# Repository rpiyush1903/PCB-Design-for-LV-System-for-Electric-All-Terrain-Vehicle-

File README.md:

# e-ATV Vehicle Control Unit (VCU)

## What this is

This is the Vehicle Control Unit (VCU) for our electric All-Terrain Vehicle, engineered specifically for the demands of e-BAJA SAE competition . The control unit should be resistant to high vibration, rough terrain, electrical noise etc.

The VCU sits at the center of the car's low-voltage control system. It reads every driver input ,ignition Key, cockpit and chassis kill switches, brake pressure switch, accelerator position sensor, and Forward/Neutral/Reverse selection(Rotary Switch) and turns that into safe, Low Voltage control over the high-voltage tractive system. It continuously monitors the safety loop, runs the basic starting and running logic of the vehicle , Controls all the Low Voltage and High Voltage components in the vehicle and is built to shut the whole tractive system down immediately if anything looks wrong.

## Hardware Design & PCB Architecture
The whole electrical layout is built with the idea of Simple , Efficient Control and Robust Safety 

The VCU PCB is made to protect the ATmega328P microcontroller from high-voltage transients, high-current switching noise, and off-road mechanical vibration through strategic domain isolation and multi-stage output driving.

## 1. Power Distribution & System Isolation

### 48V Tractive System
Powers the motor controller through a 160A main fuse, HV cut-off switch, and main Accumulator Isolation Relays (AIRs).

### 12V LV System
Stepped down via a 48V-to-12V DC-DC converter to power external safety loops, lights, RTDS buzzer, and relay coils.

### 5V Logic System
Generated by a dedicated 12V-to-5V buck converter with electrolytic (100 µF) and ceramic (0.1 µF) decoupling capacitors, providing clean power exclusively to the MCU and sensor pull-up networks.

## 2. Optocoupler & Active-LOW Output Drive

### Active-LOW Logic
GPIO output pins require  0V (LOW) signal to energize outputs. Floating pin states during bootloader execution or CPU resets cannot accidentally trigger relays.

### Galvanic Isolation
Output pins drive PC817 optocouplers, creating an optical barrier between the 5V MCU logic ground and the 12V relay ground plane.

### Low-Side Switching
Optocoupler phototransistors trigger BC547 NPN transistors to sink 12V relay coil current, keeping high current draw entirely off the 5V logic rail.

### Flyback Diode Clamping
1N4007 flyback diodes are placed in reversed manner and parallel across all relay coils to safely dissipate back-EMF inductive voltage spikes ($V = -L \frac{di}{dt}$) during de-energization, preventing CMOS latch-up.

### Digital Inputs
Brake pressure switch (A3), FNR selectors (A4/A5), and safety interlocks (A1) utilize pull-down resistor networks and hardware debouncing to guarantee stable state detection across rough terrain.

### Power Distribution

* **High Voltage Rail:** The 48V accumulator feeds through a 160A main fuse and an HV cut-off switch straight to the motor controller.
* **Low Voltage Rail:** A 48V→12V DC-DC converter powers the vehicle's 12V accessories and the dashboard safety loop.
* **Logic Power:** The ATmega328P and its supporting logic get their own dedicated 12V→5V buck converter, kept isolated from everything else on the low-voltage side.

### Core Components

* **MCU:** ATmega328P
* **Sensor Inputs:** Ignition key, cockpit and chassis kill switches, brake pressure switch, accelerator (Hall-effect sensor), and the Forward/Neutral/Reverse selector all fed from the dashboard cluster.
* **Actuator Outputs:** Relay-driven outputs for the TSAL, reverse light, main contactor (accumulator isolation relay), brake light, and the RTDS buzzer.

## Firmware Architecture

The firmware (C++, compiled through Arduino) is built with the starting sequence in mind and safety as a priority .

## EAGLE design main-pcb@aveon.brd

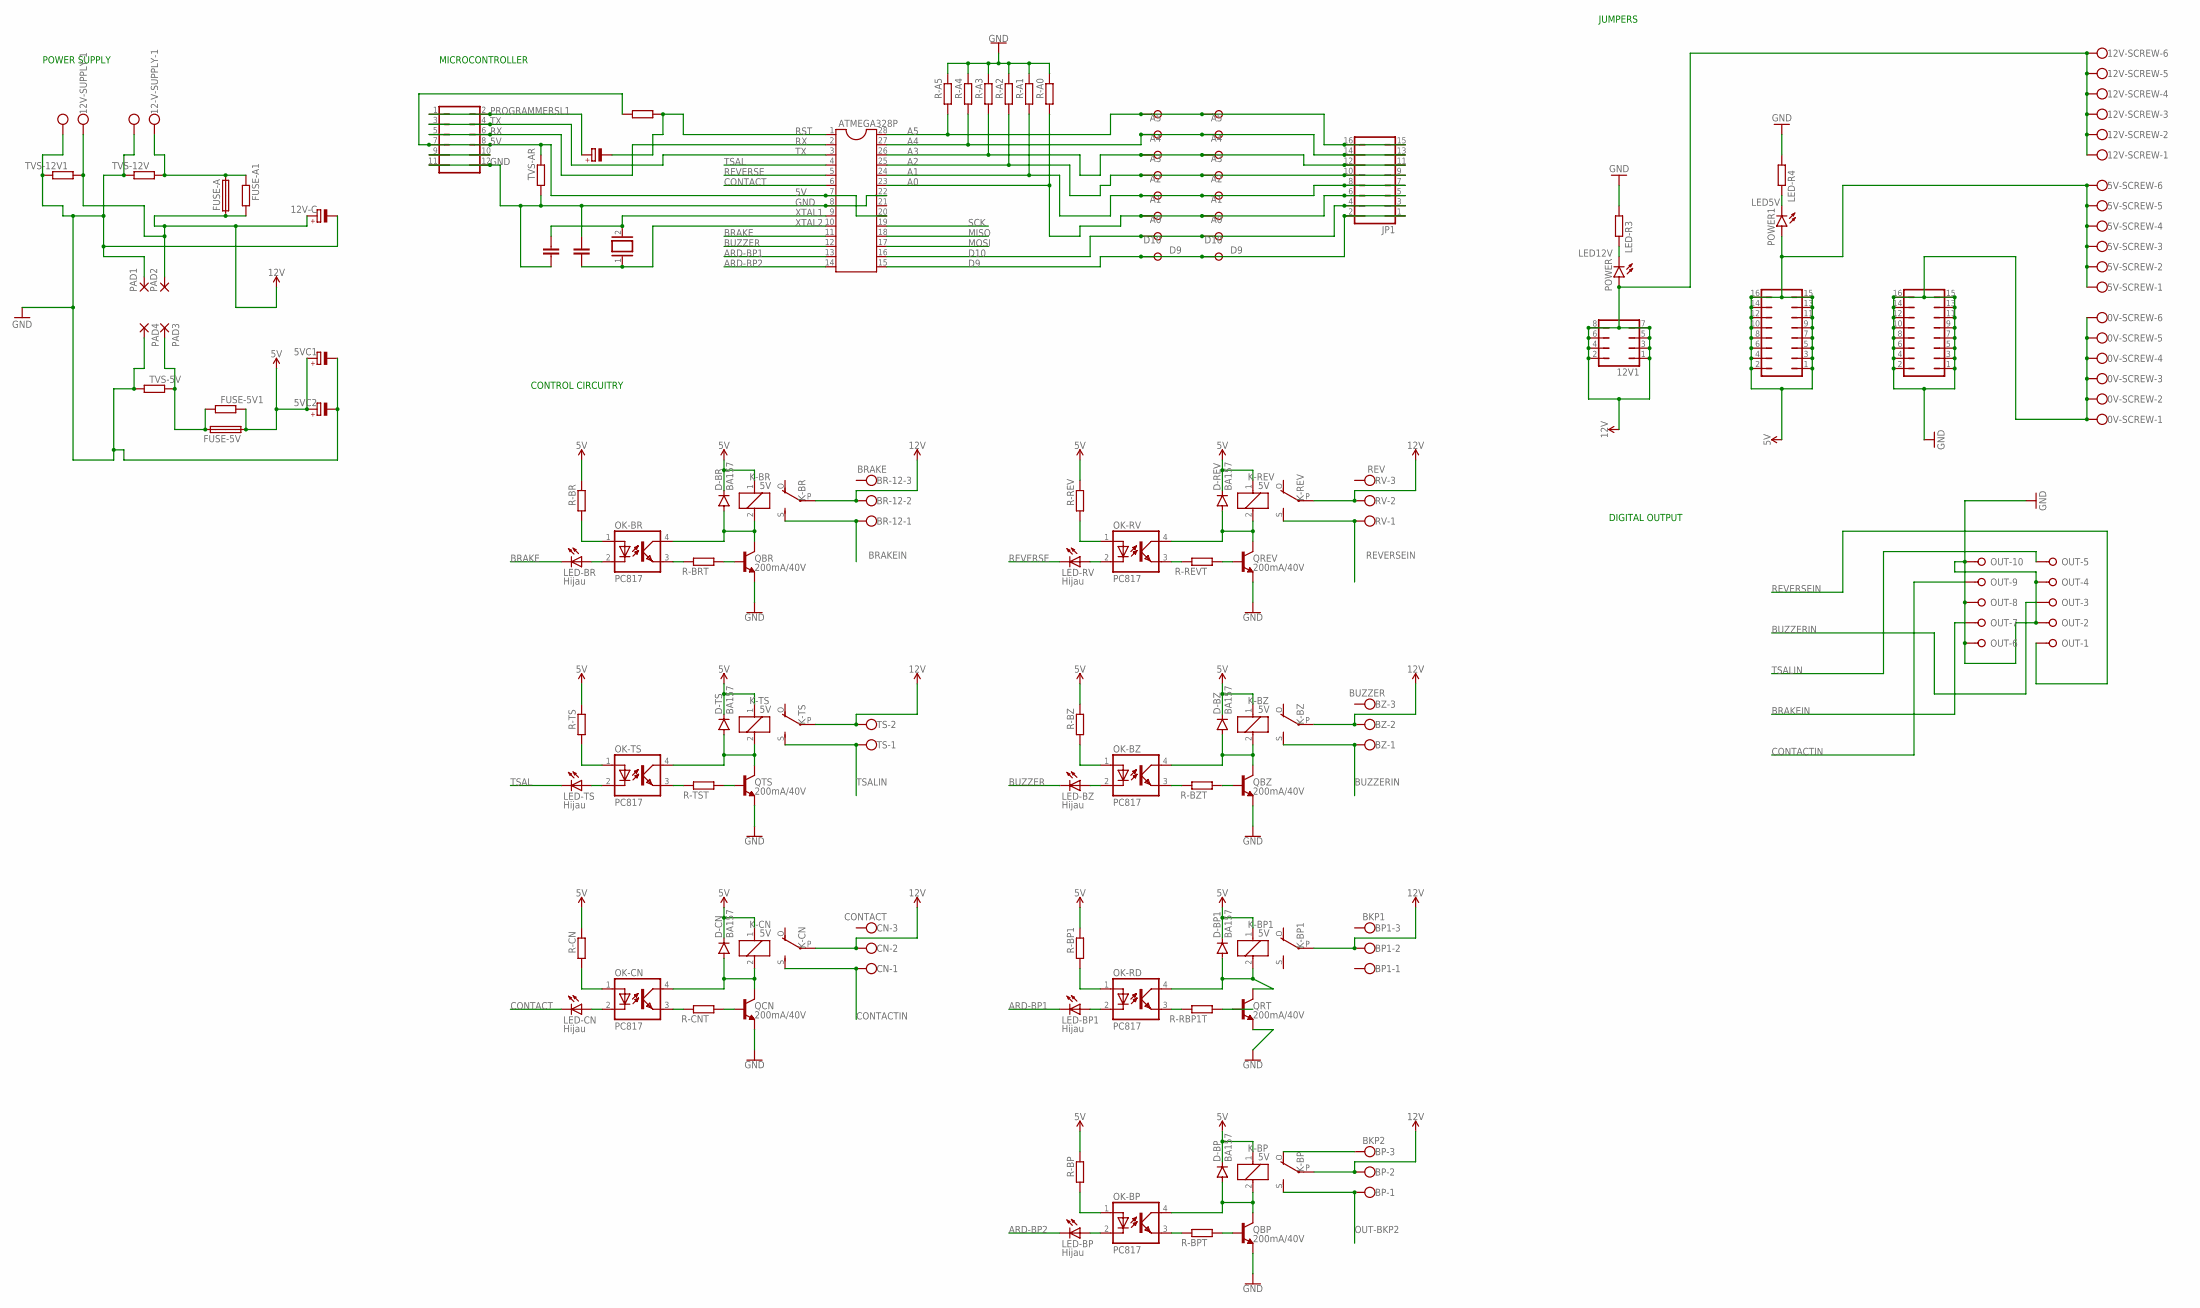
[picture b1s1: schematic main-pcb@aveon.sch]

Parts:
0V-SCREW, 5V-SCREW, 12V-SCREW: W237-6
5V, 5V1: JP8Q
5VC1, 5VC-2, 12V-C: CPOL-EUE5-10.5; E5-10,5
12-V-SUPPLY, 12V-SUPPLY: W237-102
12V1: JP4Q
A-1, A-2: W237-08P; W237-8P
ATMEGA328P: DIL28-3
BP: BKP2; W237-103
BP1: BKP1; W237-103
BR-12: BRAKE; W237-103
BZ: BUZZER; W237-103
C1, C2: C-EU025-030X050; C025-030X050
CN: CONTACT; W237-103
CRYSTAL: XTAL/S; QS
D-BP, D-BP1: BA157; P1-10
D-BR: BA157; P1-10
D-BZ: BA157; P1-10
D-CN: BA157; P1-10
D-REV: BA157; P1-10
D-TS: BA157; P1-10
FUSE-5V: SHK20L
FUSE-5V1: R-EU_0204/7; 0204/7
FUSE-A: SHK20L
FUSE-A1: R-EU_0204/7; 0204/7
JP1: JP8Q
K-BP, K-BP1: 5V; ZF112
K-BR: 5V; ZF112
K-BZ: 5V; ZF112
K-CN: 5V; ZF112
K-REV: 5V; ZF112
K-TS: 5V; ZF112
LED-BP, LED-BP1: Hijau; LED3MM
LED-BR: Hijau; LED3MM
LED-BZ: Hijau; LED3MM
LED-CN: Hijau; LED3MM
LED-R3, LED-R4: R-EU_0204/7; 0204/7
LED-RV: Hijau; LED3MM
LED-TS: Hijau; LED3MM
OK-BP: PC817; DIL04
OK-BR: PC817; DIL04
OK-BZ: PC817; DIL04
OK-CN: PC817; DIL04
OK-RD: PC817; DIL04
OK-RV: PC817; DIL04
OK-TS: PC817; DIL04
OUT: W237-10P
PAD1, PAD2, PAD3, PAD4: 2,54/1,1
POWER, POWER1: LED5MM
PROGRAMMER: JP6Q
QBP: 200mA/40V; TO-92
QBR: 200mA/40V; TO-92
QBZ: 200mA/40V; TO-92
QCN: 200mA/40V; TO-92
QREV: 200mA/40V; TO-92
QRT: 200mA/40V; TO-92
QTS: 200mA/40V; TO-92
R-A0, R-A1, R-A2, R-A3, R-A4, R-A5: R-EU_0204/7; 0204/7
R-BP, R-BP1: R-EU_0204/7; 0204/7
R-BPT: R-EU_0204/7; 0204/7
R-BR: R-EU_0204/7; 0204/7
R-BRT: R-EU_0204/7; 0204/7
R-BZ: R-EU_0204/7; 0204/7
R-BZT: R-EU_0204/7; 0204/7
R-CN: R-EU_0204/7; 0204/7
R-CNT: R-EU_0204/7; 0204/7
R-RBP1T: R-EU_0204/7; 0204/7
R-REV: R-EU_0204/7; 0204/7
R-REVT: R-EU_0204/7; 0204/7
R-TS: R-EU_0204/7; 0204/7
R-TST: R-EU_0204/7; 0204/7
RST-C: CPOL-EUE2.5-6; E2,5-6
RST-R: R-EU_0204/7; 0204/7
RV: REV; W237-103
TS: TSAL; W237-103
TVS-5V, TVS-12V, TVS-12V1: R-EU_0204/7; 0204/7
TVS-AR: R-EU_0204/7; 0204/7

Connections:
5V: 5V.1, 5V.2, 5V.3, 5V.4, 5V.5, 5V.6, 5V.7, 5V.8, 5V.9, 5V.10, 5V.11, 5V.12, 5V.13, 5V.14, 5V.15, 5V.16, 5V-SCREW.1, 5V-SCREW.2, 5V-SCREW.3, 5V-SCREW.4, 5V-SCREW.5, 5V-SCREW.6, 5VC1.+, 5VC-2.+, ATMEGA328P.7, ATMEGA328P.20, D-BP.C, D-BP1.C, D-BR.C, D-BZ.C, D-CN.C, D-REV.C, D-TS.C, FUSE-5V.1A, FUSE-5V1.2, K-BP.1, K-BP1.1, K-BR.1, K-BZ.1, K-CN.1, K-REV.1, K-TS.1, POWER1.A, PROGRAMMER.7, PROGRAMMER.8, R-BP.2, R-BP1.2, R-BR.2, R-BZ.2, R-CN.2, R-REV.2, R-TS.2, RST-R.1, TVS-AR.2
12V: 12V1.1, 12V1.2, 12V1.3, 12V1.4, 12V1.5, 12V1.6, 12V1.7, 12V1.8, 12V-C.+, 12V-SCREW.1, 12V-SCREW.2, 12V-SCREW.3, 12V-SCREW.4, 12V-SCREW.5, 12V-SCREW.6, 12V-SUPPLY.1, BP.2, BP1.2, BR-12.2, BZ.2, CN.2, FUSE-A.1A, FUSE-A1.1, K-BP.P, K-BP1.P, K-BR.P, K-BZ.P, K-CN.P, K-REV.P, K-TS.P, PAD2.1, POWER.A, RV.2, TS.2, TVS-12V1.1
A0: A-1.3, A-2.3, ATMEGA328P.23, JP1.5, JP1.6, R-A0.1
A1: A-1.4, A-2.4, ATMEGA328P.24, JP1.7, JP1.8, R-A1.1
A2: A-1.5, A-2.5, ATMEGA328P.25, JP1.9, JP1.10, R-A2.1
A3: A-1.6, A-2.6, ATMEGA328P.26, JP1.11, JP1.12, R-A3.1
A4: A-1.7, A-2.7, ATMEGA328P.27, JP1.13, JP1.14, R-A4.1
A5: A-1.8, A-2.8, ATMEGA328P.28, JP1.15, JP1.16, R-A5.1
ARD-BP1: ATMEGA328P.13, LED-BP1.K (C)
ARD-BP2: ATMEGA328P.14, LED-BP.K (C)
BRAKE: ATMEGA328P.11, LED-BR.K (C)
BRAKEIN: BR-12.1, K-BR.S, OUT.7
BUZZER: ATMEGA328P.12, LED-BZ.K (C)
BUZZERIN: BZ.1, K-BZ.S, OUT.3
CONTACT: ATMEGA328P.6, LED-CN.K (C)
CONTACTIN: CN.1, K-CN.S, OUT.9
D9: A-1.1, A-2.1, ATMEGA328P.15, JP1.1, JP1.2
D10: A-1.2, A-2.2, ATMEGA328P.16, JP1.3, JP1.4
GND: 0V-SCREW.1, 0V-SCREW.2, 0V-SCREW.3, 0V-SCREW.4, 0V-SCREW.5, 0V-SCREW.6, 5V1.1, 5V1.2, 5V1.3, 5V1.4, 5V1.5, 5V1.6, 5V1.7, 5V1.8, 5V1.9, 5V1.10, 5V1.11, 5V1.12, 5V1.13, 5V1.14, 5V1.15, 5V1.16, 5VC1.-, 5VC-2.-, 12-V-SUPPLY.2, 12V-C.-, 12V-SUPPLY.2, ATMEGA328P.8, ATMEGA328P.22, C1.1, C2.2, LED-R3.1, LED-R4.1, OUT.2, OUT.4, OUT.6, OUT.8, OUT.10, PAD1.1, PAD4.1, PROGRAMMER.11, PROGRAMMER.12, QBP.1 (E), QBR.1 (E), QBZ.1 (E), QCN.1 (E), QREV.1 (E), QRT.1 (E), QTS.1 (E), R-A0.2, R-A1.2, R-A2.2, R-A3.2, R-A4.2, R-A5.2, TVS-5V.1, TVS-12V.2, TVS-12V1.2, TVS-AR.1
LED5V: LED-R4.2, POWER1.K (C)
LED12V: LED-R3.2, POWER.K (C)
MISO: ATMEGA328P.18
MOSI: ATMEGA328P.17
unnamed: 12-V-SUPPLY.1, FUSE-A.2A, FUSE-A1.2, TVS-12V.1
unnamed: OK-BR.1 (A), R-BR.1
unnamed: FUSE-5V.2A, FUSE-5V1.1, PAD3.1, TVS-5V.2
unnamed: OK-RV.1 (A), R-REV.1
unnamed: LED-RV.A, OK-RV.2 (C)
unnamed: LED-BR.A, OK-BR.2 (C)
unnamed: OK-BR.3 (EMIT), R-BRT.2
unnamed: D-BR.A, K-BR.2, OK-BR.4 (COL), QBR.3 (C)
unnamed: QBR.2 (B), R-BRT.1
unnamed: OK-TS.1 (A), R-TS.1
unnamed: LED-TS.A, OK-TS.2 (C)
unnamed: OK-TS.3 (EMIT), R-TST.2
unnamed: QTS.2 (B), R-TST.1
unnamed: D-TS.A, K-TS.2, OK-TS.4 (COL), QTS.3 (C)
unnamed: OK-RV.3 (EMIT), R-REVT.2
unnamed: QREV.2 (B), R-REVT.1
unnamed: D-REV.A, K-REV.2, OK-RV.4 (COL), QREV.3 (C)
unnamed: OK-BZ.1 (A), R-BZ.1
unnamed: LED-BZ.A, OK-BZ.2 (C)
unnamed: OK-BZ.3 (EMIT), R-BZT.2
unnamed: QBZ.2 (B), R-BZT.1
unnamed: D-BZ.A, K-BZ.2, OK-BZ.4 (COL), QBZ.3 (C)
unnamed: OK-CN.1 (A), R-CN.1
unnamed: LED-CN.A, OK-CN.2 (C)
unnamed: OK-CN.3 (EMIT), R-CNT.2
unnamed: QCN.2 (B), R-CNT.1
unnamed: D-CN.A, K-CN.2, OK-CN.4 (COL), QCN.3 (C)
unnamed: OK-RD.1 (A), R-BP1.1
unnamed: LED-BP1.A, OK-RD.2 (C)
unnamed: OK-RD.3 (EMIT), R-RBP1T.2
unnamed: QRT.2 (B), R-RBP1T.1
unnamed: D-BP1.A, K-BP1.2, OK-RD.4 (COL), QRT.3 (C)
unnamed: OK-BP.1 (A), R-BP.1
unnamed: LED-BP.A, OK-BP.2 (C)
unnamed: OK-BP.3 (EMIT), R-BPT.2
unnamed: QBP.2 (B), R-BPT.1
unnamed: D-BP.A, K-BP.2, OK-BP.4 (COL), QBP.3 (C)
unnamed: PROGRAMMER.9, PROGRAMMER.10
unnamed: BP.3, K-BP.O
OUT-BKP2: BP.1, K-BP.S
PROGRAMMERSL1: PROGRAMMER.1, PROGRAMMER.2, RST-C.+
REVERSE: ATMEGA328P.5, LED-RV.K (C)
REVERSEIN: K-REV.S, OUT.1, RV.1
RST: ATMEGA328P.1, RST-C.-, RST-R.2
RX: ATMEGA328P.2, PROGRAMMER.5, PROGRAMMER.6
SCK: ATMEGA328P.19
TSAL: ATMEGA328P.4, LED-TS.K (C)
TSALIN: K-TS.S, OUT.5, TS.1
TX: ATMEGA328P.3, PROGRAMMER.3, PROGRAMMER.4
XTAL1: ATMEGA328P.9, C1.2, CRYSTAL.2
XTAL2: ATMEGA328P.10, C2.1, CRYSTAL.1

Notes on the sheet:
POWER SUPPLY
MICROCONTROLLER
CONTROL CIRCUITRY
JUMPERS
DIGITAL OUTPUT

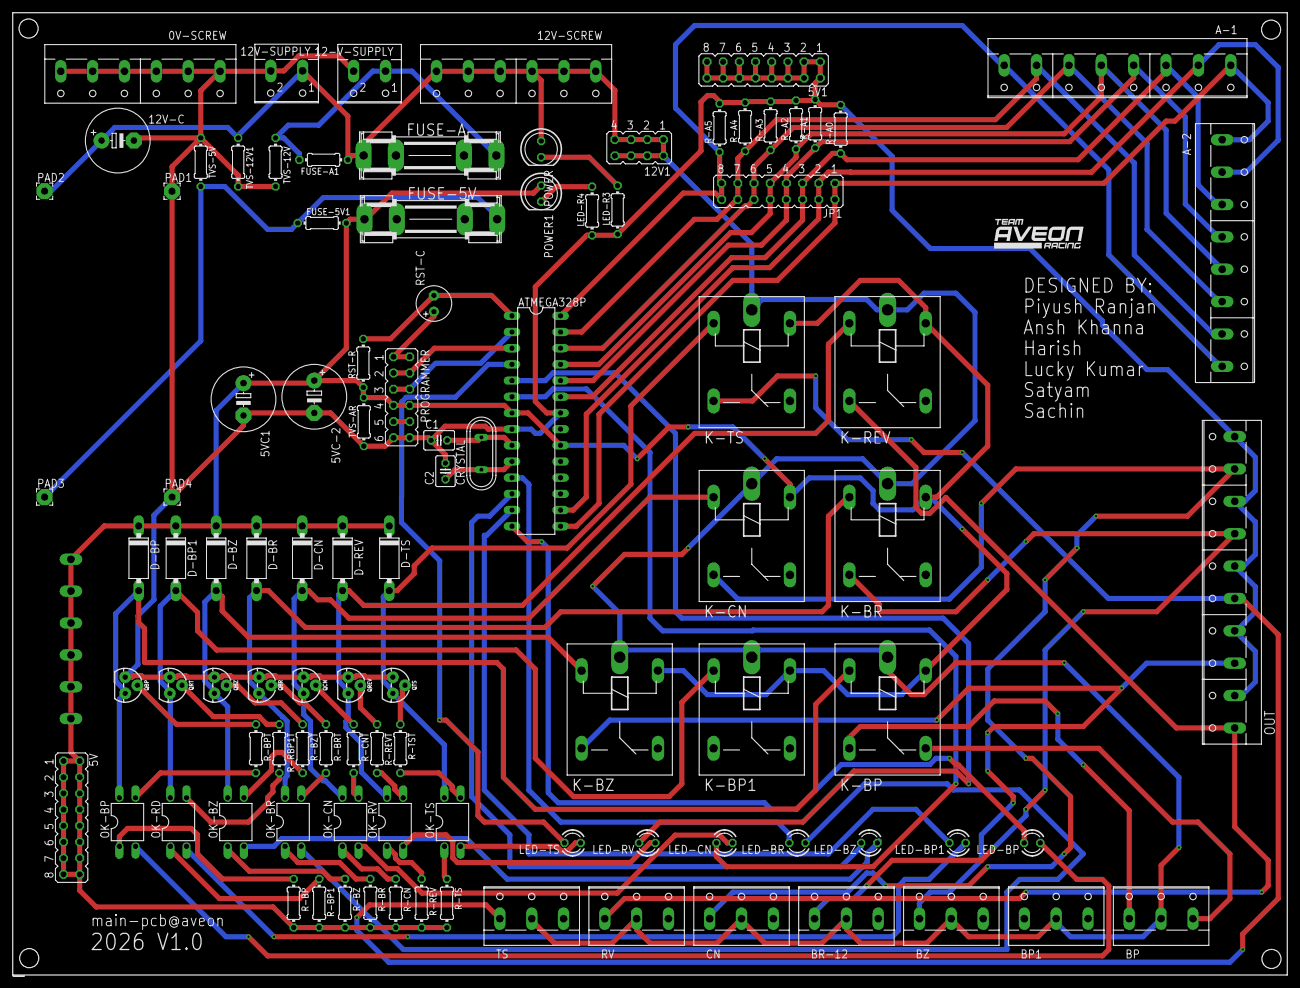
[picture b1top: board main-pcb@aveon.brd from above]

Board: 2 copper layers, 200.0 x 151.0 mm, 100 parts (1 on the bottom side), 71 nets.

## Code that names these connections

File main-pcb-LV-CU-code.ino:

/* * PROJECT: Team AVEON Racing VCU - FINAL HARDWARE ADAPTED
 * * HARDWARE SPECIFIC FIXES:
 * 1. START BUTTON (Pin A0):
 * - Active HIGH (5V = Pressed).
 * - Non-latching (Press once to Latch System ON).
 * 2. TSAL "STROBE" FIX: 
 * - Pulse Relay ON for 1000ms, OFF for 100ms to skip the light's built-in pause.
 * * * STANDARD COMPLIANCE:
 * - Kill Switch: Instant cut (Rule 13).
 * - RTDS: 2s Continuous (Rule C.5.7).
 * - Reverse Alarm: Beeps in Reverse (Rule B.10.4.3).
 */

#include <Arduino.h>

// ================================================================
// 1. PIN CONFIGURATION
// ================================================================

// INPUTS
const int PIN_START_BTN = A0; // Start Button (Active HIGH: 5V = Pressed)
const int PIN_KILL      = A1; // Kill Switch (Active HIGH)
const int PIN_ACCEL     = A2; // Analog Accelerator
const int PIN_BRAKE     = A3; // Brake Switch (Active HIGH)
const int PIN_REVERSE   = A4; // Reverse Switch (Active HIGH)
const int PIN_NEUTRAL   = A5; // Neutral Switch (Active HIGH)

// OUTPUTS (Active LOW: 0V = ON/Relay Closed)
const int PIN_TSAL        = 2; 
const int PIN_REV_LIGHT   = 3; 
const int PIN_CONTACT     = 4; // Main AIR Relay
const int PIN_BRAKE_LIGHT = 5; 
const int PIN_RTDS        = 6; // Buzzer Relay

// ================================================================
// 2. TUNING PARAMETERS
// ================================================================

// Throttle Safety
const int ACCEL_THRESHOLD = 50;   

// --- TSAL "RESET" TIMING (CRITICAL FOR YOUR LIGHT) ---
// Your light blinks for 1 second, then pauses. 
// We keep it ON for 1000ms, then OFF for 100ms to restart it.
const unsigned long TSAL_ACTIVE_MS = 1000; // Duration of the "5 blinks"
const unsigned long TSAL_RESET_MS  = 100;  // Quick power cut to reset cycle

// RTDS: 2 Seconds Continuous (Rule C.5.7)
const unsigned long RTDS_DURATION = 2000; 

// REVERSE ALARM: Beep Speed
const unsigned long REV_BEEP_INTERVAL = 500;

// ================================================================
// 3. GLOBAL VARIABLES
// ================================================================

bool vehicleActive = false;       // System Latch State
bool rtdsActive = false;          
unsigned long rtdsStartTime = 0;  
unsigned long lastRevBeepTime = 0; 

// TSAL Timing Variables
unsigned long lastTsalSwitchTime = 0;
bool tsalRelayState = HIGH; // HIGH = OFF, LOW = ON

int revBeepState = HIGH; 

// ================================================================
// 4. SETUP
// ================================================================
void setup() {
  // Inputs
  pinMode(PIN_KILL, INPUT);
  pinMode(PIN_START_BTN, INPUT); 
  pinMode(PIN_ACCEL, INPUT); 
  pinMode(PIN_BRAKE, INPUT);
  pinMode(PIN_REVERSE, INPUT);
  pinMode(PIN_NEUTRAL, INPUT);

  // Outputs
  pinMode(PIN_BRAKE_LIGHT, OUTPUT);
  pinMode(PIN_TSAL, OUTPUT);
  pinMode(PIN_REV_LIGHT, OUTPUT);
  pinMode(PIN_RTDS, OUTPUT);
  pinMode(PIN_CONTACT, OUTPUT);

  // SAFE INITIAL STATE (All OFF)
  digitalWrite(PIN_CONTACT, HIGH);      
  digitalWrite(PIN_TSAL, HIGH);         
  digitalWrite(PIN_RTDS, HIGH);         
  digitalWrite(PIN_BRAKE_LIGHT, HIGH);  
  digitalWrite(PIN_REV_LIGHT, HIGH);    
  
  Serial.begin(9600);
}

// ================================================================
// 5. MAIN LOOP
// ================================================================
void loop() {
  
  // --- A. READ SENSORS ---
  // Start Button Logic: HIGH = Pressed (Active HIGH 5V)
  bool isStartPressed= (digitalRead(PIN_START_BTN) == HIGH); 
  
  // Other Inputs (Assumed Active HIGH based on context)
  bool isKillPressed = (digitalRead(PIN_KILL) == HIGH); 
  bool isBrakePressed= (digitalRead(PIN_BRAKE) == HIGH);
  bool isNeutral     = (digitalRead(PIN_NEUTRAL) == HIGH);
  bool isReverse     = (digitalRead(PIN_REVERSE) == HIGH);
  
  int accelRaw = analogRead(PIN_ACCEL);
  bool isThrottleZero = (accelRaw < ACCEL_THRESHOLD); 

  // --- B. INDEPENDENT LIGHT LOGIC ---
  
  // Brake Light (Rule 13 Exception: Works even if Killed)
  if (isBrakePressed) digitalWrite(PIN_BRAKE_LIGHT, LOW); 
  else digitalWrite(PIN_BRAKE_LIGHT, HIGH);

  // Reverse Light (Rule 13: Must Turn OFF if Killed)
  if (isReverse && !isKillPressed) digitalWrite(PIN_REV_LIGHT, LOW); 
  else digitalWrite(PIN_REV_LIGHT, HIGH); 

  // --- C. SHARED BUZZER LOGIC ---
  int buzzerSignal = HIGH; 

  // Priority 1: RTDS (Continuous on Start)
  if (rtdsActive && !isKillPressed) {
    if (millis() - rtdsStartTime < RTDS_DURATION) {
      buzzerSignal = LOW; // ON (Continuous)
    } else {
      rtdsActive = false; 
      buzzerSignal = HIGH; 
    }
  } 
  // Priority 2: Reverse Alarm (Beeping)
  else if (isReverse && !isKillPressed) {
    if (millis() - lastRevBeepTime >= REV_BEEP_INTERVAL) {
      lastRevBeepTime = millis();
      revBeepState = (revBeepState == HIGH) ? LOW : HIGH;
    }
    buzzerSignal = revBeepState;
  } 
  else {
    buzzerSignal = HIGH; // Quiet
    revBeepState = HIGH; 
  }
  digitalWrite(PIN_RTDS, buzzerSignal);

  // --- D. SAFETY SHUTDOWN CHECK ---
  // Rule 13: Kill Switch de-energizes Tractive System & TSAL
  if (isKillPressed) {
    vehicleActive = false; // Unlatch system
    
    digitalWrite(PIN_CONTACT, HIGH); // AIR OFF
    digitalWrite(PIN_TSAL, HIGH);    // TSAL OFF
    rtdsActive = false;
  }

  // --- E. STARTING SEQUENCE (Rule 12) ---
  else if (!vehicleActive) {
    // Logic: Neutral + Brake + Zero Throttle + Not Reverse + START BUTTON PRESS
    if (isNeutral && isBrakePressed && isThrottleZero && !isReverse && isStartPressed) {
      
      vehicleActive = true; // LATCH: System stays ON after this
      
      digitalWrite(PIN_CONTACT, LOW); // Energize AIR
      
      // Trigger RTDS
      rtdsActive = true;
      rtdsStartTime = millis();
      
      // Reset TSAL Timer
      lastTsalSwitchTime = millis();
      tsalRelayState = LOW; // Start ON immediately
    }
  }

  // --- F. ACTIVE VEHICLE BEHAVIOR ---
  if (vehicleActive) {
    digitalWrite(PIN_CONTACT, LOW); // Keep AIR ON

    // *** TSAL "RELAY RESET" LOGIC ***
    // This fixes the "1 second pause" issue of your hardware light.
    unsigned long tsalCurrentTime = millis();
    
    if (tsalRelayState == LOW) {
      // CURRENTLY ON: Wait for the 5 blinks to finish (1000ms)
      if (tsalCurrentTime - lastTsalSwitchTime >= TSAL_ACTIVE_MS) {
        lastTsalSwitchTime = tsalCurrentTime;
        tsalRelayState = HIGH; // Turn OFF briefly to reset light
      }
    } else {
      // CURRENTLY OFF: Wait for reset (100ms) then turn back ON
      if (tsalCurrentTime - lastTsalSwitchTime >= TSAL_RESET_MS) {
        lastTsalSwitchTime = tsalCurrentTime;
        tsalRelayState = LOW; // Turn ON to restart blink cycle
      }
    }
    digitalWrite(PIN_TSAL, tsalRelayState);
    
  } else {
    // Standby Mode
    digitalWrite(PIN_CONTACT, HIGH);
    digitalWrite(PIN_TSAL, HIGH);
  }
}

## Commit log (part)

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2026-01-20 Add files via upload
    image of board file made on eagle software

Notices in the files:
parts and their libraries:
SparkFun-DiscreteSemi: Licensing: Creative Commons ShareAlike 4.0 International - https://creativecommons.org/licenses/by-sa/4.0
